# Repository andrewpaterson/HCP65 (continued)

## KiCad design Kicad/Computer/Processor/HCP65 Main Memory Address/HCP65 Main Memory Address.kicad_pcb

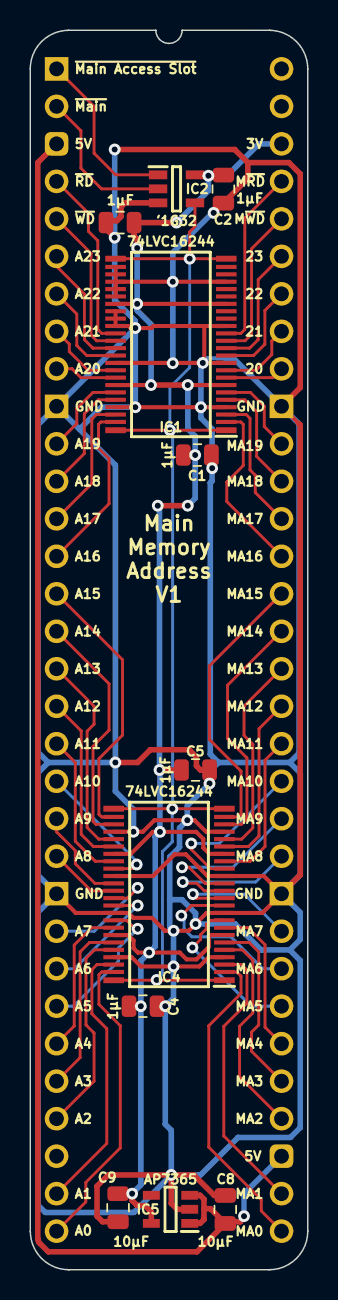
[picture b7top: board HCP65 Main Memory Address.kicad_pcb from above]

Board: 2 copper layers, 18.8 x 84.0 mm, 12 parts (0 on the bottom side), 58 nets.

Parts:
C1, C2, C3, C4, C5: 1μF; C_0805
C8, C9: 10µF; C_0805
IC1, IC4: 74LVC16244ADGG,112; 74LVC16244ADGG112
IC2: 74LVC1G32GV,125; SOT95P275X110-5N
IC5: AP7365-33WG-7; SOT95P285X130-5N
J2: Board 2x32 W15.24mm; DIP-64_Board_W15.24mm

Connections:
3.3V: C1.1, C2.1, C3.1, C4.1, C5.1, C9.1, IC1.7 (3V), IC1.18 (3V), IC1.31 (3V), IC1.42 (3V), IC2.5 (3V), IC4.7 (3V), IC4.18 (3V), IC4.31 (3V), IC4.42 (3V), IC5.5 (3.3VOut), J2.62
5V: C8.1, IC5.1 (6VIn), IC5.3 (EN), J2.3, J2.35
/~Main Access: IC1.1 (1~OE), IC1.24 (4~OE), IC1.25 (3~OE), IC1.48 (2~OE), IC2.4 (Y), IC4.1 (1~OE), IC4.24 (4~OE), IC4.25 (3~OE), IC4.48 (2~OE)
A0: IC4.47 (1A0), J2.32
A1: IC4.46 (1A1), J2.31
A2: IC4.44 (1A2), J2.29
A3: IC4.43 (1A3), J2.28
A4: IC4.41 (2A0), J2.27
A5: IC4.40 (2A1), J2.26
A6: IC4.38 (2A2), J2.25
A7: IC4.37 (2A3), J2.24
A8: IC4.36 (3A0), J2.22
A9: IC4.35 (3A1), J2.21
A10: IC4.33 (3A2), J2.20
A11: IC4.32 (3A3), J2.19
A12: IC4.30 (4A0), J2.18
A13: IC4.29 (4A1), J2.17
A14: IC4.27 (4A2), J2.16
A15: IC4.26 (4A3), J2.15
A16: IC1.47 (1A0), J2.14
A17: IC1.46 (1A1), J2.13
A18: IC1.44 (1A2), J2.12
A19: IC1.43 (1A3), J2.11
A20: IC1.41 (2A0), J2.9
A21: IC1.40 (2A1), J2.8
A22: IC1.38 (2A2), J2.7
A23: IC1.37 (2A3), J2.6
GND: C1.2, C2.2, C3.2, C4.2, C5.2, C8.2, C9.2, IC1.4 (GND), IC1.10 (GND), IC1.15 (GND), IC1.21 (GND), IC1.26 (4A3), IC1.27 (4A2), IC1.28 (GND), IC1.29 (4A1), IC1.30 (4A0), IC1.32 (3A3), IC1.33 (3A2), IC1.34 (GND), IC1.39 (GND), IC1.45 (GND), IC2.3 (GND), IC4.4 (GND), IC4.10 (GND), IC4.15 (GND), IC4.21 (GND), IC4.28 (GND), IC4.34 (GND), IC4.39 (GND), IC4.45 (GND), IC5.2 (GND), J2.10, J2.23, J2.42, J2.55
MA0: IC4.2 (1Y0), J2.33
MA1: IC4.3 (1Y1), J2.34
MA2: IC4.5 (1Y2), J2.36
MA3: IC4.6 (1Y3), J2.37
MA4: IC4.8 (2Y0), J2.38
MA5: IC4.9 (2Y1), J2.39
MA6: IC4.11 (2Y2), J2.40
MA7: IC4.12 (2Y3), J2.41
MA8: IC4.13 (3Y0), J2.43
MA9: IC4.14 (3Y1), J2.44
MA10: IC4.16 (3Y2), J2.45
MA11: IC4.17 (3Y3), J2.46
MA12: IC4.19 (4Y0), J2.47
MA13: IC4.20 (4Y1), J2.48
MA14: IC4.22 (4Y2), J2.49
MA15: IC4.23 (4Y3), J2.50
MA16: IC1.2 (1Y0), J2.51
MA17: IC1.3 (1Y1), J2.52
MA18: IC1.5 (1Y2), J2.53
MA19: IC1.6 (1Y3), J2.54
MA20: IC1.8 (2Y0), J2.56
MA21: IC1.9 (2Y1), J2.57
MA22: IC1.11 (2Y2), J2.58
MA23: IC1.12 (2Y3), J2.59
~Main RD: IC1.14 (3Y1), J2.61
~Main Slot: IC2.1 (B), J2.1
~Main WD: IC1.13 (3Y0), J2.60
~Main: IC2.2 (A), J2.2
~RD: IC1.35 (3A1), J2.4
~WD: IC1.36 (3A0), J2.5

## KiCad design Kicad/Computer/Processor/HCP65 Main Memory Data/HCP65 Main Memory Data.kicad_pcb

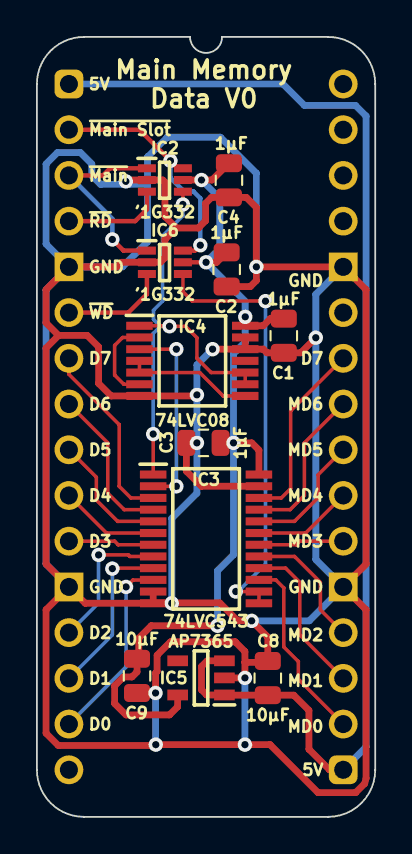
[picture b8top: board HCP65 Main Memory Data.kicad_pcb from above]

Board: 2 copper layers, 18.8 x 43.3 mm, 12 parts (0 on the bottom side), 28 nets.

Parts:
C1, C2, C3, C4: 1μF; C_0805
C8, C9: 10µF; C_0805
IC2, IC6: SN74LVC1G332DCKR; SOT65P210X110-6N
IC3: SN74LVC543APWR; SOP65P640X120-24N
IC4: 74LVC08APW,112; SOP65P640X110-14N
IC5: AP7365-33WG-7; SOT95P285X130-5N
J5: Board 2x16 W15.24mm; DIP-32_Board_W15.24mm

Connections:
5V: C8.1, IC5.1 (6VIn), IC5.3 (EN), J5.1, J5.17
/3.3V: C1.1, C2.1, C3.1, C4.1, C9.1, IC2.5 (3V), IC3.24 (3V), IC4.14 (3V), IC5.5 (3.3VOut), IC6.5 (3V)
/~Read: IC2.4 (Y), IC3.1 (~LEB), IC4.1 (1A), IC4.9 (3A), IC4.10 (3B)
/~Read_{2}: IC4.4 (2A), IC4.5 (2B), IC4.8 (3Y)
/~Read_{3}: IC4.2 (1B), IC4.6 (2Y)
/~Read_{4}: IC3.2 (~OEA), IC4.3 (1Y)
/~Write: IC3.13 (~OEB), IC3.14 (~LEA), IC6.4 (Y)
D0: IC3.10 (A8), J5.15
D1: IC3.9 (A7), J5.14
D2: IC3.8 (A6), J5.13
D3: IC3.7 (A5), J5.11
D4: IC3.6 (A4), J5.10
D5: IC3.5 (A3), J5.9
D6: IC3.4 (A2), J5.8
D7: IC3.3 (A1), J5.7
GND: C1.2, C2.2, C3.2, C4.2, C8.2, C9.2, IC2.2 (GND), IC3.11 (~CEAB), IC3.12 (GND), IC3.23 (~CEBA), IC4.7 (GND), IC4.12 (4A), IC4.13 (4B), IC5.2 (GND), IC6.2 (GND), J5.5, J5.12, J5.21, J5.28
MD0: IC3.15 (B8), J5.18
MD1: IC3.16 (B7), J5.19
MD2: IC3.17 (B6), J5.20
MD3: IC3.18 (B5), J5.22
MD4: IC3.19 (B4), J5.23
MD5: IC3.20 (B3), J5.24
MD6: IC3.21 (B2), J5.25
MD7: IC3.22 (B1), J5.26
~Main RD: IC2.3 (B), J5.4
~Main Slot: IC2.6 (C), IC6.6 (C), J5.2
~Main WD: IC6.3 (B), J5.6
~Main: IC2.1 (A), IC6.1 (A), J5.3
